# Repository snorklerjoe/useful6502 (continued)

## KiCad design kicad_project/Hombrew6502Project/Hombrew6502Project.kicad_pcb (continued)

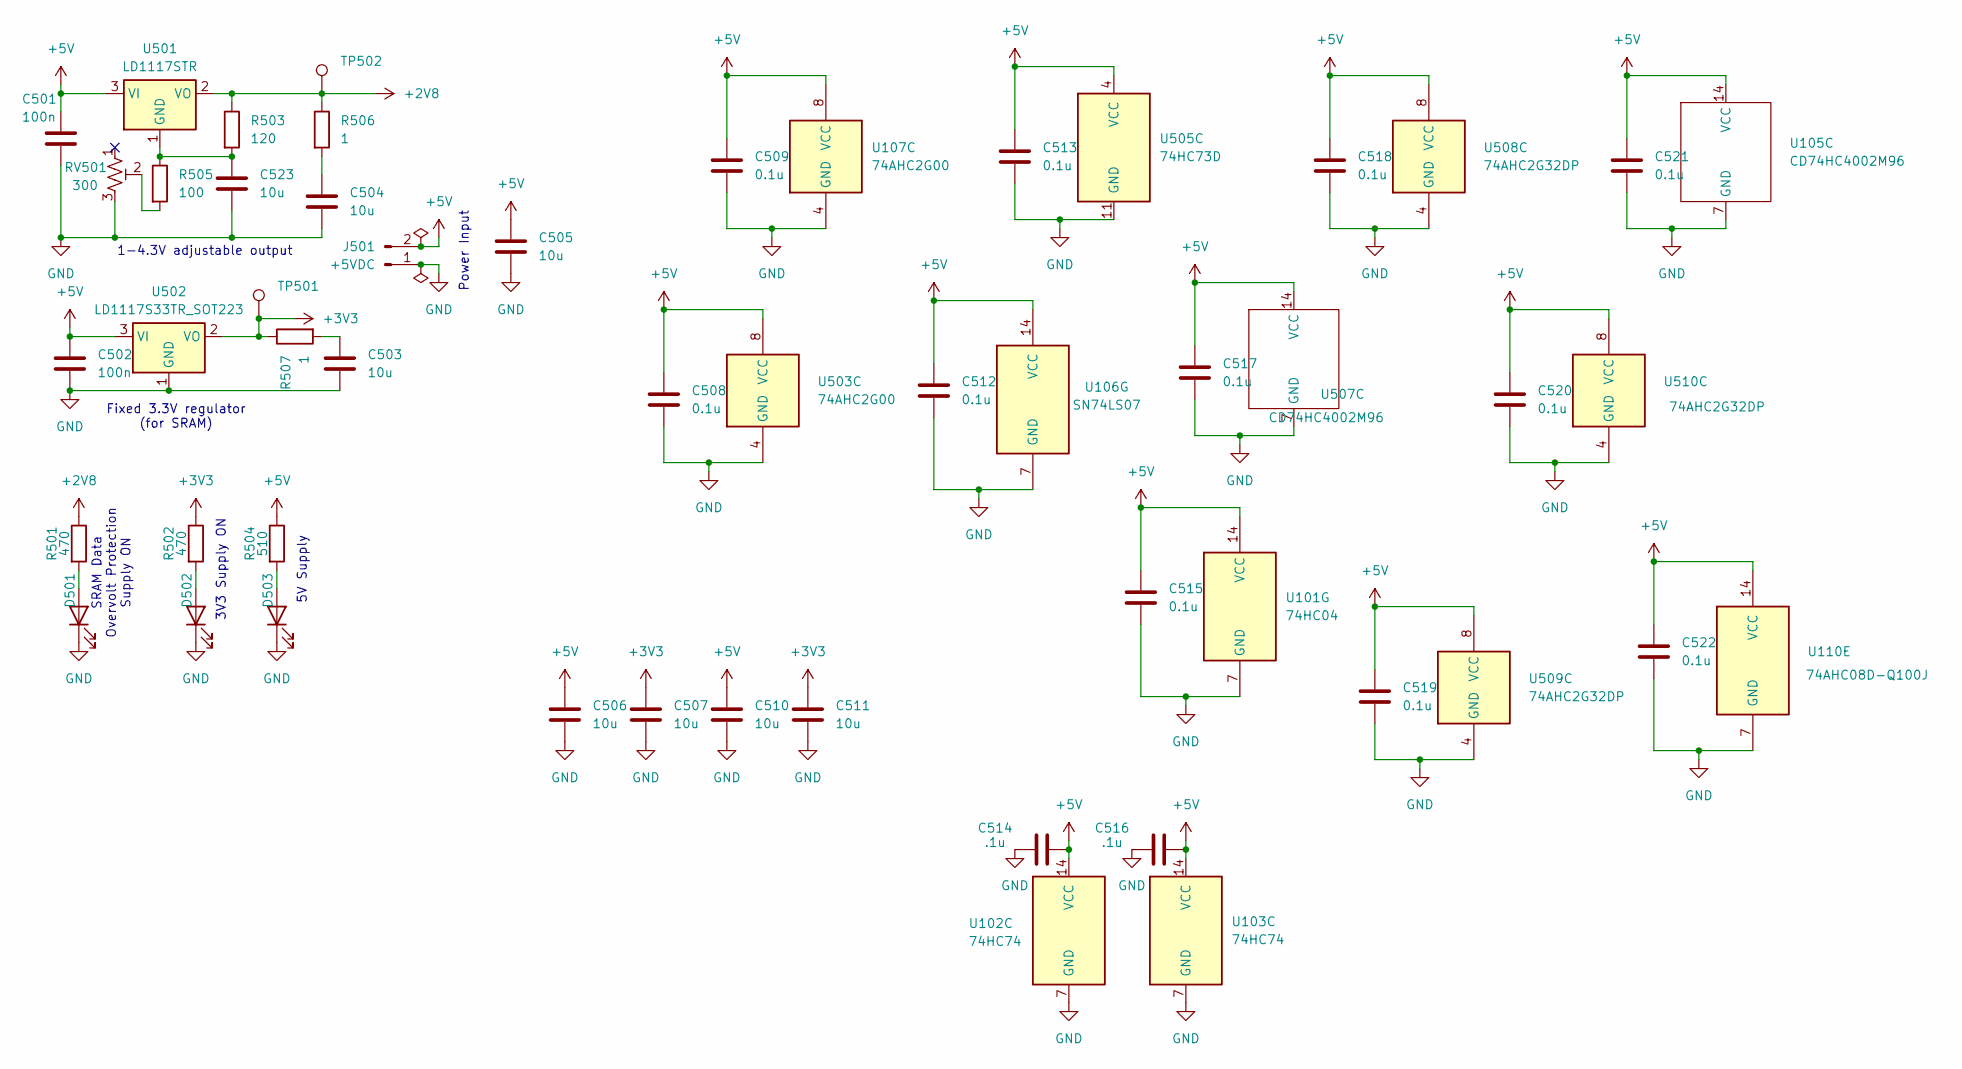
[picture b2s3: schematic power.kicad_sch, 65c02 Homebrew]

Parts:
C501, C502: 100n; C_0402_1005Metric
C503, C504, C505, C506, C507, C510, C511, C523: 10u; C_0402_1005Metric
C508, C509, C512, C513, C515, C517, C518, C519, C520, C521, C522: 0.1u; C_0402_1005Metric
C514, C516: .1u; C_0402_1005Metric
D501, D502, D503: LED; LED_0402_1005Metric
J501: +5VDC; PinHeader_1x02_P2.54mm_Vertical
R501, R502: 470; R_0402_1005Metric
R503: 120; R_0402_1005Metric
R504: 510; R_0402_1005Metric
R505: 100; R_0402_1005Metric
R506, R507: 1; R_0402_1005Metric
RV501: 300; Potentiometer_Bourns_TC33X_Vertical
TP501, TP502: TestPoint; TestPoint_Pad_D2.5mm
U101: 74HC04; SOIC-14_3.9x8.7mm_P1.27mm
U102, U103: 74HC74; SOIC-14_3.9x8.7mm_P1.27mm
U105, U507: CD74HC4002M96; SOIC-14_3.9x8.7mm_P1.27mm
U106: SN74LS07; SOIC-14_3.9x8.7mm_P1.27mm
U107, U503: 74AHC2G00; TSSOP-8_3x3mm_P0.65mm
U110: 74AHC08D-Q100J; SOIC-14_3.9x8.7mm_P1.27mm
U501: LD1117STR; SOT-223-3_TabPin2
U502: LD1117S33TR_SOT223; SOT-223-3_TabPin2
U505: 74HC73D; SOIC-14_3.9x8.7mm_P1.27mm
U508, U509, U510: 74AHC2G32DP; TSSOP-8_3x3mm_P0.65mm

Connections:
+2V8: R501.1, R503.1, R506.1, TP502.1, U501.2 (VO); also elsewhere on the board
+3V3: C507.1, C511.1, R502.1, R507.1, TP501.1, U502.2 (VO); also elsewhere on the board
+5V: C501.1, C502.1, C505.1, C506.1, C508.1, C509.1, C510.1, C512.1, C513.1, C514.1, C515.1, C516.1, C517.1, C518.1, C519.1, C520.1, C521.1, C522.1, J501.2, R504.1, U101.14 (VCC), U102.14 (VCC), U103.14 (VCC), U105.14 (VCC), U106.14 (VCC), U107.8 (VCC), U110.14 (VCC), U501.3 (VI), U502.3 (VI), U503.8 (VCC), U505.4 (VCC), U507.14 (VCC), U508.8 (VCC), U509.8 (VCC), U510.8 (VCC); also elsewhere on the board
GND: C501.2, C502.2, C503.2, C504.2, C505.2, C506.2, C507.2, C508.2, C509.2, C510.2, C511.2, C512.2, C513.2, C514.2, C515.2, C516.2, C517.2, C518.2, C519.2, C520.2, C521.2, C522.2, C523.2, D501.1 (K), D502.1 (K), D503.1 (K), J501.1, RV501.3, U101.7 (GND), U102.7 (GND), U103.7 (GND), U105.7 (GND), U106.7 (GND), U107.4 (GND), U110.7 (GND), U502.1 (GND), U503.4 (GND), U505.11 (GND), U507.7 (GND), U508.4 (GND), U509.4 (GND), U510.4 (GND); also elsewhere on the board
unnamed: C503.1, R507.2
unnamed: C504.1, R506.2
unnamed: D501.2 (A), R501.2
unnamed: D502.2 (A), R502.2
unnamed: D503.2 (A), R504.2
unnamed: R505.2, RV501.2
unnamed: C523.1, R503.2, R505.1, U501.1 (GND)

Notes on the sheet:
Fixed 3.3V regulator (for SRAM)
1-4.3V adjustable output
SRAM Data Overvolt Protection Supply ON
Power Input
5V Supply
3V3 Supply ON

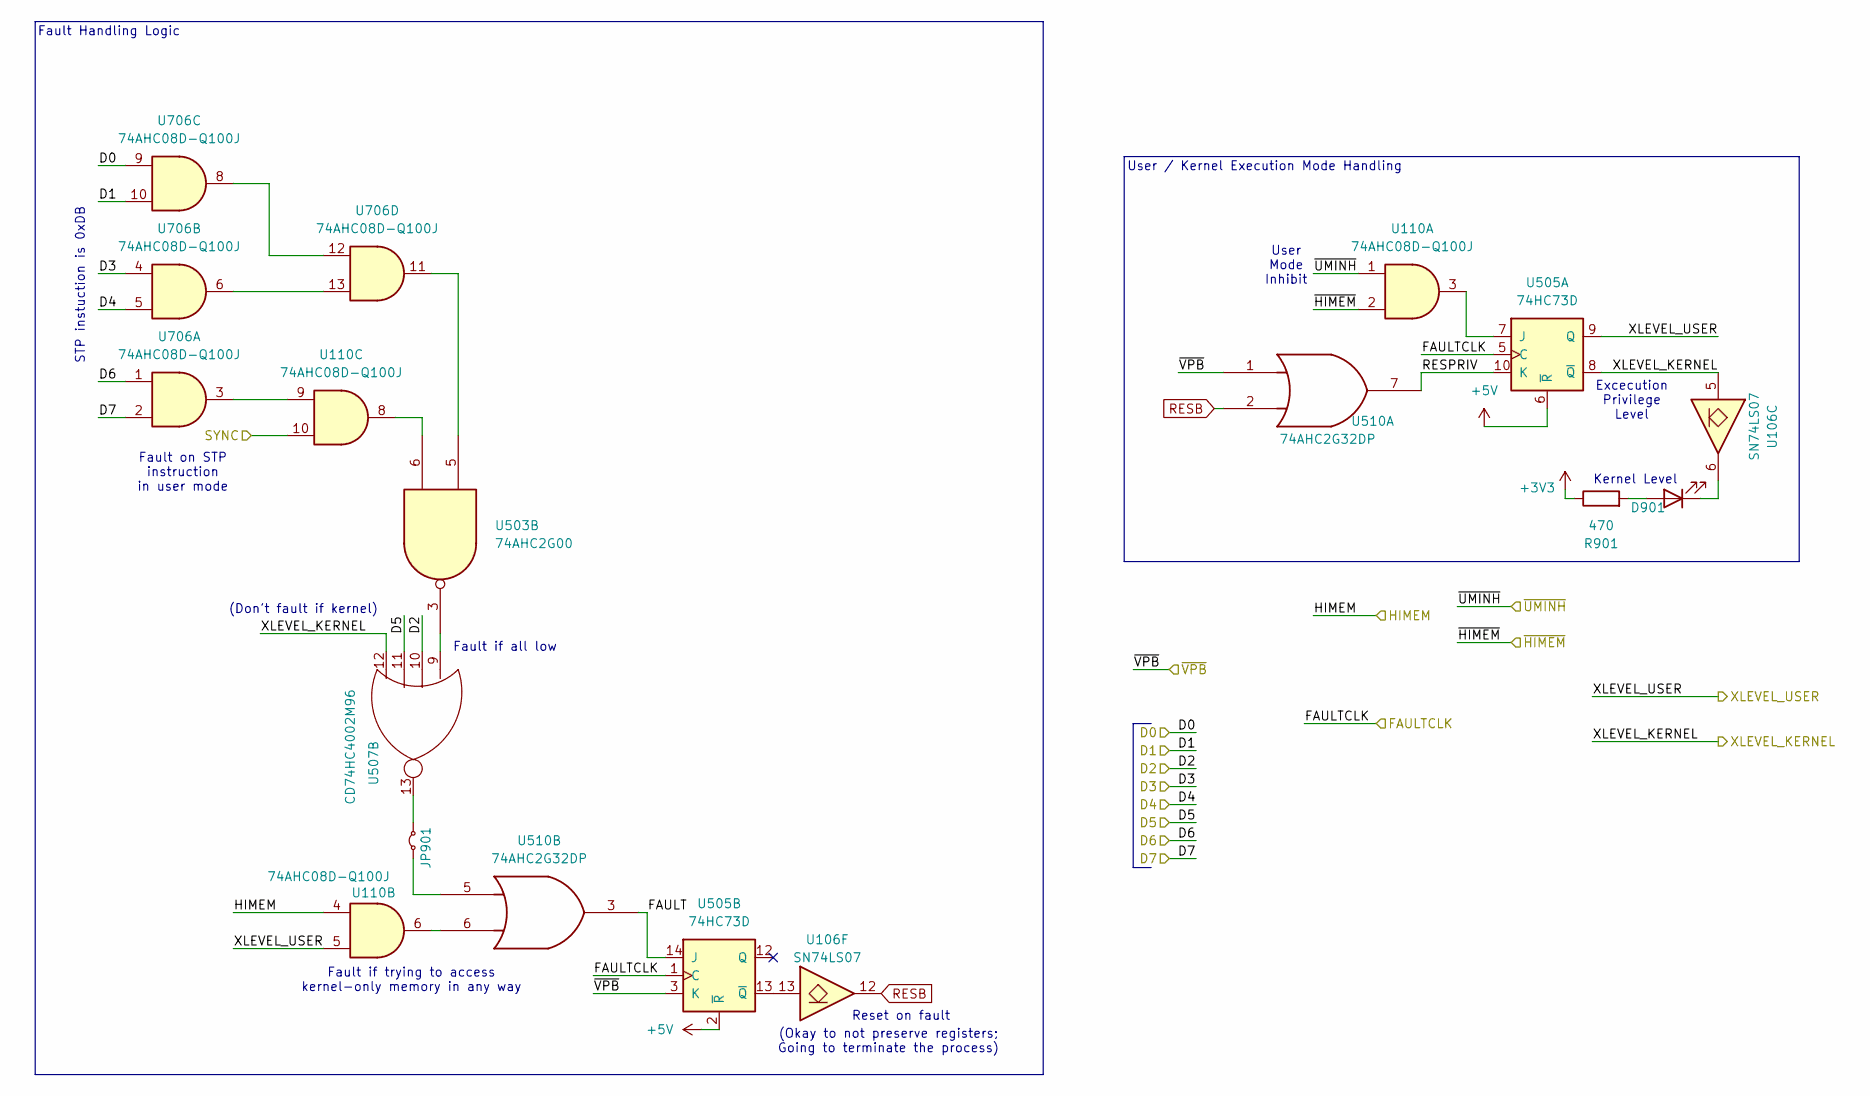
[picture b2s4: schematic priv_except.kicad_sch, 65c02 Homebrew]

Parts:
D901: LED; LED_0402_1005Metric
JP901: Jumper_2_Small_Bridged; SolderJumper-2_P1.3mm_Bridged2Bar_Pad1.0x1.5mm
R901: 470; R_0402_1005Metric
U106: SN74LS07; SOIC-14_3.9x8.7mm_P1.27mm
U110, U706: 74AHC08D-Q100J; SOIC-14_3.9x8.7mm_P1.27mm
U503: 74AHC2G00; TSSOP-8_3x3mm_P0.65mm
U505: 74HC73D; SOIC-14_3.9x8.7mm_P1.27mm
U507: CD74HC4002M96; SOIC-14_3.9x8.7mm_P1.27mm
U510: 74AHC2G32DP; TSSOP-8_3x3mm_P0.65mm

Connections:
+3V3: R901.1; also elsewhere on the board
+5V: U505.2 (~R), U505.6 (~R); also elsewhere on the board
/D0: U706.9; also elsewhere on the board
/D1: U706.10; also elsewhere on the board
/D2: U507.10; also elsewhere on the board
/D3: U706.4; also elsewhere on the board
/D4: U706.5; also elsewhere on the board
/D5: U507.11; also elsewhere on the board
/D6: U706.1; also elsewhere on the board
/D7: U706.2; also elsewhere on the board
/FAULTCLK: U505.1 (C), U505.5 (C); also elsewhere on the board
/HIMEM: U110.4; also elsewhere on the board
/Privileges & Exception Handling/FAULT: U505.14 (J), U510.3
/Privileges & Exception Handling/RESPRIV: U505.10 (K), U510.7
/SYNC: U110.10; also elsewhere on the board
/XLEVEL_KERNEL: U106.5, U505.8 (~Q), U507.12
/XLEVEL_USER: U110.5, U505.9 (Q)
/~HIMEM: U110.2; also elsewhere on the board
/~UMINH: U110.1; also elsewhere on the board
/~VPB: U505.3 (K), U510.1; also elsewhere on the board
unnamed: D901.2 (A), R901.2
unnamed: D901.1 (K), U106.6
unnamed: JP901.1 (A), U510.5
unnamed: JP901.2 (B), U507.13
unnamed: U110.6, U510.6
unnamed: U110.8, U503.6
unnamed: U110.9, U706.3
unnamed: U503.3, U507.9
unnamed: U503.5, U706.11
unnamed: U110.3, U505.7 (J)
unnamed: U106.13, U505.13 (~Q)
unnamed: U706.8, U706.12
unnamed: U706.6, U706.13
RESB: U106.12, U510.2; also elsewhere on the board

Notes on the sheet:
User Mode Inhibit
Kernel Level
Fault if trying to access kernel-only memory in any way
User / Kernel Execution Mode Handling
(Don't fault if kernel)
Fault if all low
Reset on fault
(Okay to not preserve registers; Going to terminate the process)
Fault on STP instruction in user mode
STP instuction is 0xDB
Excecution Privilege Level
Fault Handling Logic

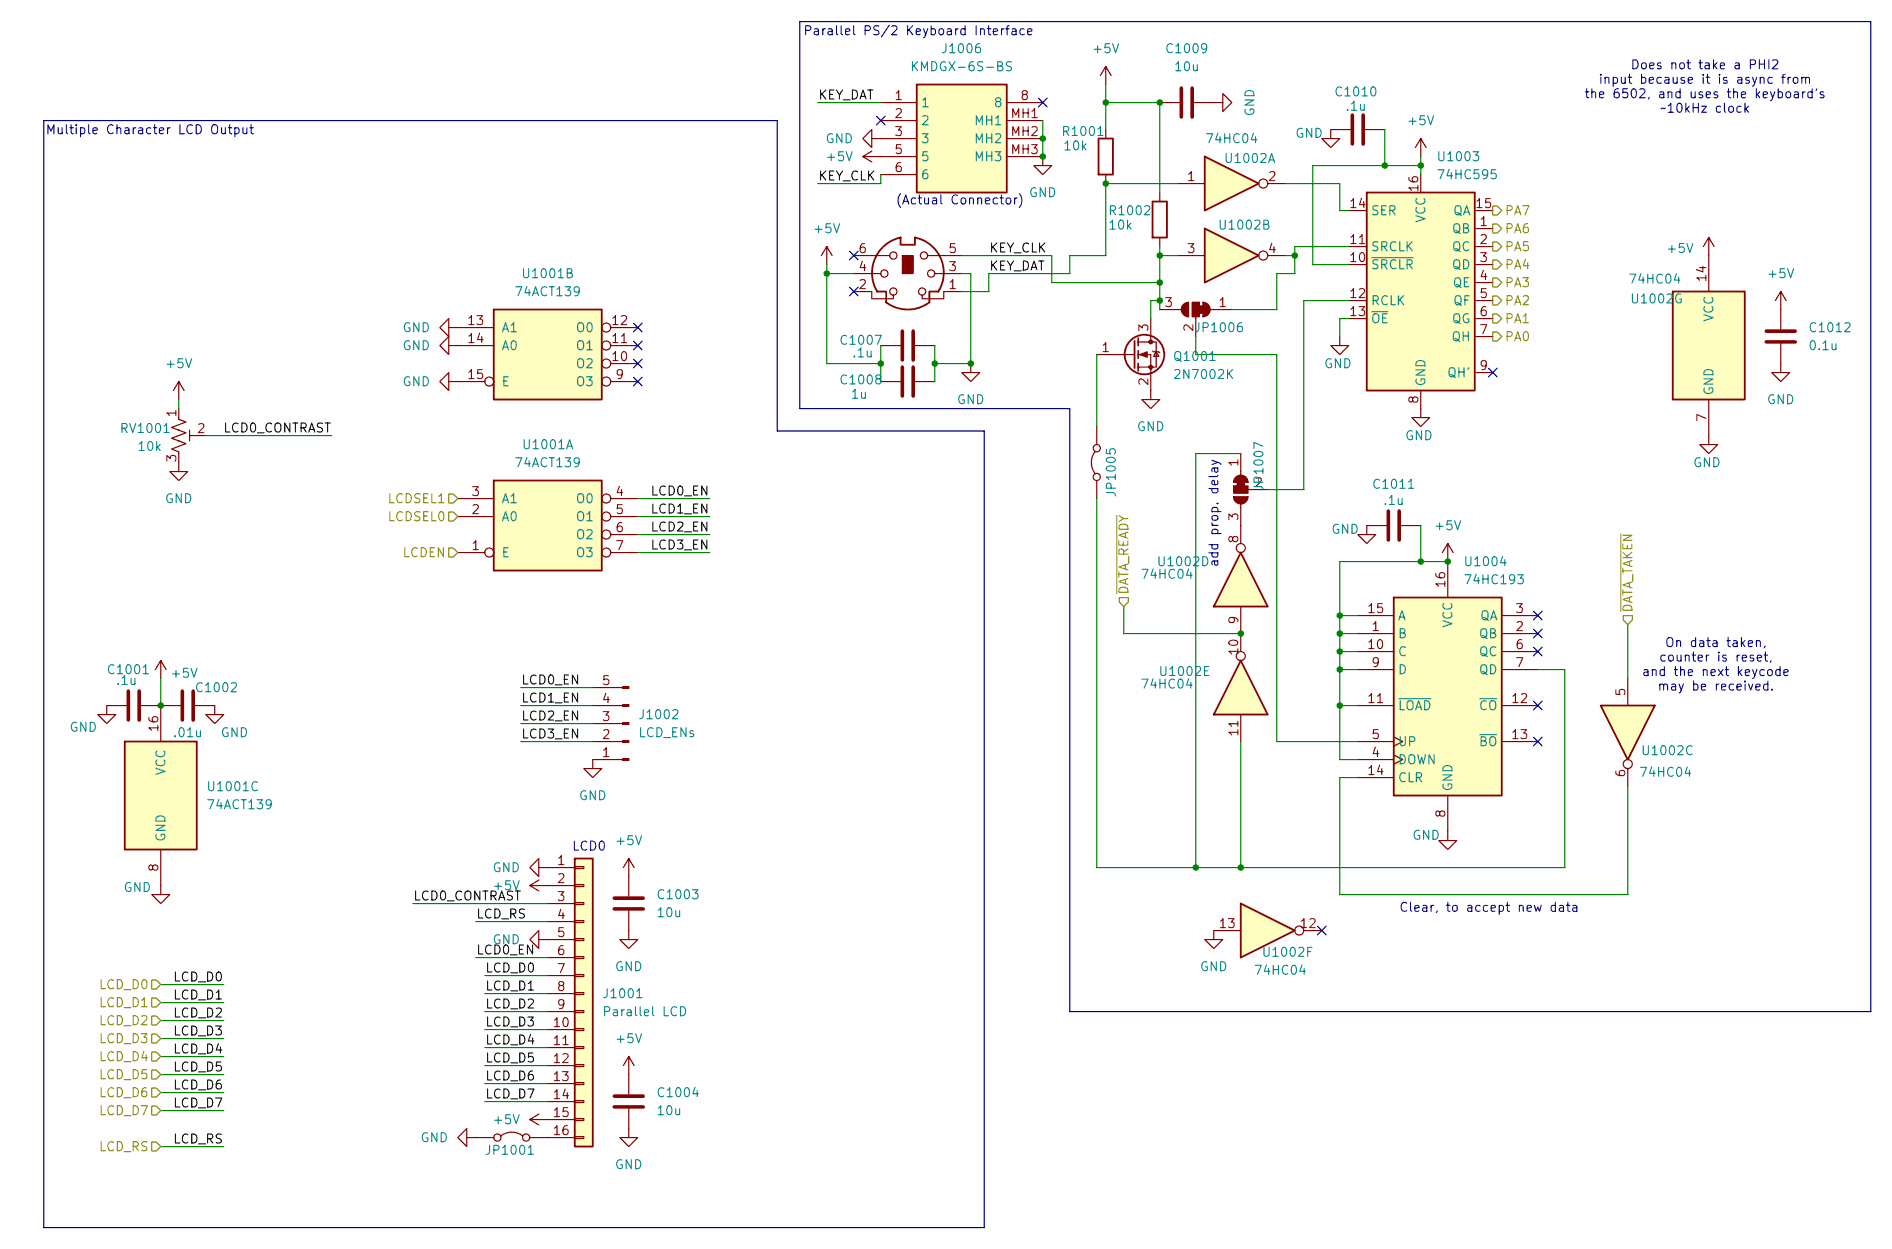
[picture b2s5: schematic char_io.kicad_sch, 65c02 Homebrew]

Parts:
C1001, C1007, C1010, C1011: .1u; C_0402_1005Metric
C1002: .01u; C_0402_1005Metric
C1003, C1004, C1009: 10u; C_0402_1005Metric
C1008: 1u; C_0402_1005Metric
C1012: 0.1u; C_0402_1005Metric
J1001: Parallel LCD; IDC-Header_2x08_P2.54mm_Vertical_SMD
J1002: LCD_ENs; PinHeader_1x05_P2.54mm_Vertical
J1005: KMDGX-6S-BS
J1006: KMDGX-6S-BS; KMDGX6SBS; Mouser Part Number 806-KMDGX-6S-BS
JP1001, JP1005: Jumper_2_Bridged; SolderJumper-2_P1.3mm_Bridged2Bar_Pad1.0x1.5mm
JP1006, JP1007: SolderJumper_3_Bridged12; SolderJumper-3_P1.3mm_Bridged12_Pad1.0x1.5mm
Q1001: 2N7002K; SOT-23
R1001, R1002: 10k; R_0402_1005Metric
RV1001: 10k; Potentiometer_Bourns_TC33X_Vertical
U1001: 74ACT139; TSSOP-16_4.4x5mm_P0.65mm
U1002: 74HC04; SOIC-14_3.9x8.7mm_P1.27mm
U1003: 74HC595; SOIC-16_3.9x9.9mm_P1.27mm
U1004: 74HC193; TSSOP-16_4.4x5mm_P0.65mm

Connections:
+5V: C1001.2, C1002.1, C1003.1, C1004.1, C1007.1, C1008.1, C1009.1, C1010.2, C1011.2, C1012.1, J1001.2, J1001.15, J1005.4, J1006.5, R1001.1, R1002.1, RV1001.1, U1001.16 (VCC), U1002.14 (VCC), U1003.10 (~SRCLR), U1003.16 (VCC), U1004.1 (B), U1004.4 (DOWN), U1004.9 (D), U1004.10 (C), U1004.11 (~LOAD), U1004.15 (A), U1004.16 (VCC); also elsewhere on the board
/Character IO/KEY_CLK: J1005.5, J1006.6, JP1006.3 (B), Q1001.3 (D), R1002.2, U1002.3
/Character IO/KEY_DAT: J1005.1, J1006.1, R1001.2, U1002.1
/Character IO/LCD0_CONTRAST: J1001.3, RV1001.2
/Character IO/LCD0_EN: J1001.6, J1002.5, U1001.4 (O0)
/Character IO/LCD1_EN: J1002.4, U1001.5 (O1)
/Character IO/LCD2_EN: J1002.3, U1001.6 (O2)
/Character IO/LCD3_EN: J1002.2, U1001.7 (O3)
/Character IO/LCDEN: U1001.1 (E); also elsewhere on the board
/Character IO/LCDSEL0: U1001.2 (A0); also elsewhere on the board
/Character IO/LCDSEL1: U1001.3 (A1); also elsewhere on the board
/Character IO/LCD_RS: J1001.4; also elsewhere on the board
/Character IO/PA0: U1003.7 (QH); also elsewhere on the board
/Character IO/PA1: U1003.6 (QG); also elsewhere on the board
/Character IO/PA2: U1003.5 (QF); also elsewhere on the board
/Character IO/PA3: U1003.4 (QE); also elsewhere on the board
/Character IO/PA4: U1003.3 (QD); also elsewhere on the board
/Character IO/PA5: U1003.2 (QC); also elsewhere on the board
/Character IO/PA6: U1003.1 (QB); also elsewhere on the board
/Character IO/PA7: U1003.15 (QA); also elsewhere on the board
/Character IO/~DATA_READY: U1002.9, U1002.10; also elsewhere on the board
/Character IO/~DATA_TAKEN: U1002.5; also elsewhere on the board
/PQ0: J1001.7; also elsewhere on the board
/PQ1: J1001.8; also elsewhere on the board
/PQ2: J1001.9; also elsewhere on the board
/PQ3: J1001.10; also elsewhere on the board
/PQ4: J1001.11; also elsewhere on the board
/PQ5: J1001.12; also elsewhere on the board
/PQ6: J1001.13; also elsewhere on the board
/PQ7: J1001.14; also elsewhere on the board
GND: C1001.1, C1002.2, C1003.2, C1004.2, C1007.2, C1008.2, C1009.2, C1010.1, C1011.1, C1012.2, J1001.1, J1001.5, J1002.1, J1005.3, J1006.3, J1006.MH1, J1006.MH2, J1006.MH3, JP1001.1 (A), Q1001.2 (S), RV1001.3, U1001.8 (GND), U1001.13 (A1), U1001.14 (A0), U1001.15 (E), U1002.7 (GND), U1002.13, U1003.8 (GND), U1003.13 (~OE), U1004.8 (GND); also elsewhere on the board
unnamed: J1001.16, JP1001.2 (B)
unnamed: JP1005.1 (A), JP1007.1 (A), U1002.11, U1004.7 (QD)
unnamed: JP1005.2 (B), Q1001.1 (G)
unnamed: JP1006.1 (A), U1002.4, U1003.11 (SRCLK)
unnamed: JP1006.2 (C), U1004.5 (UP)
unnamed: JP1007.3 (B), U1002.8
unnamed: JP1007.2 (C), U1003.12 (RCLK)
unnamed: U1002.2, U1003.14 (SER)
unnamed: U1002.6, U1004.14 (CLR)

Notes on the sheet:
On data taken, counter is reset, and the next keycode may be received.
(Actual Connector)
Clear, to accept new data
Multiple Character LCD Output
Parallel PS/2 Keyboard Interface
add prop. delay
LCD0
Does not take a PHI2 input because it is async from the 6502, and uses the keyboard's ~10kHz clock

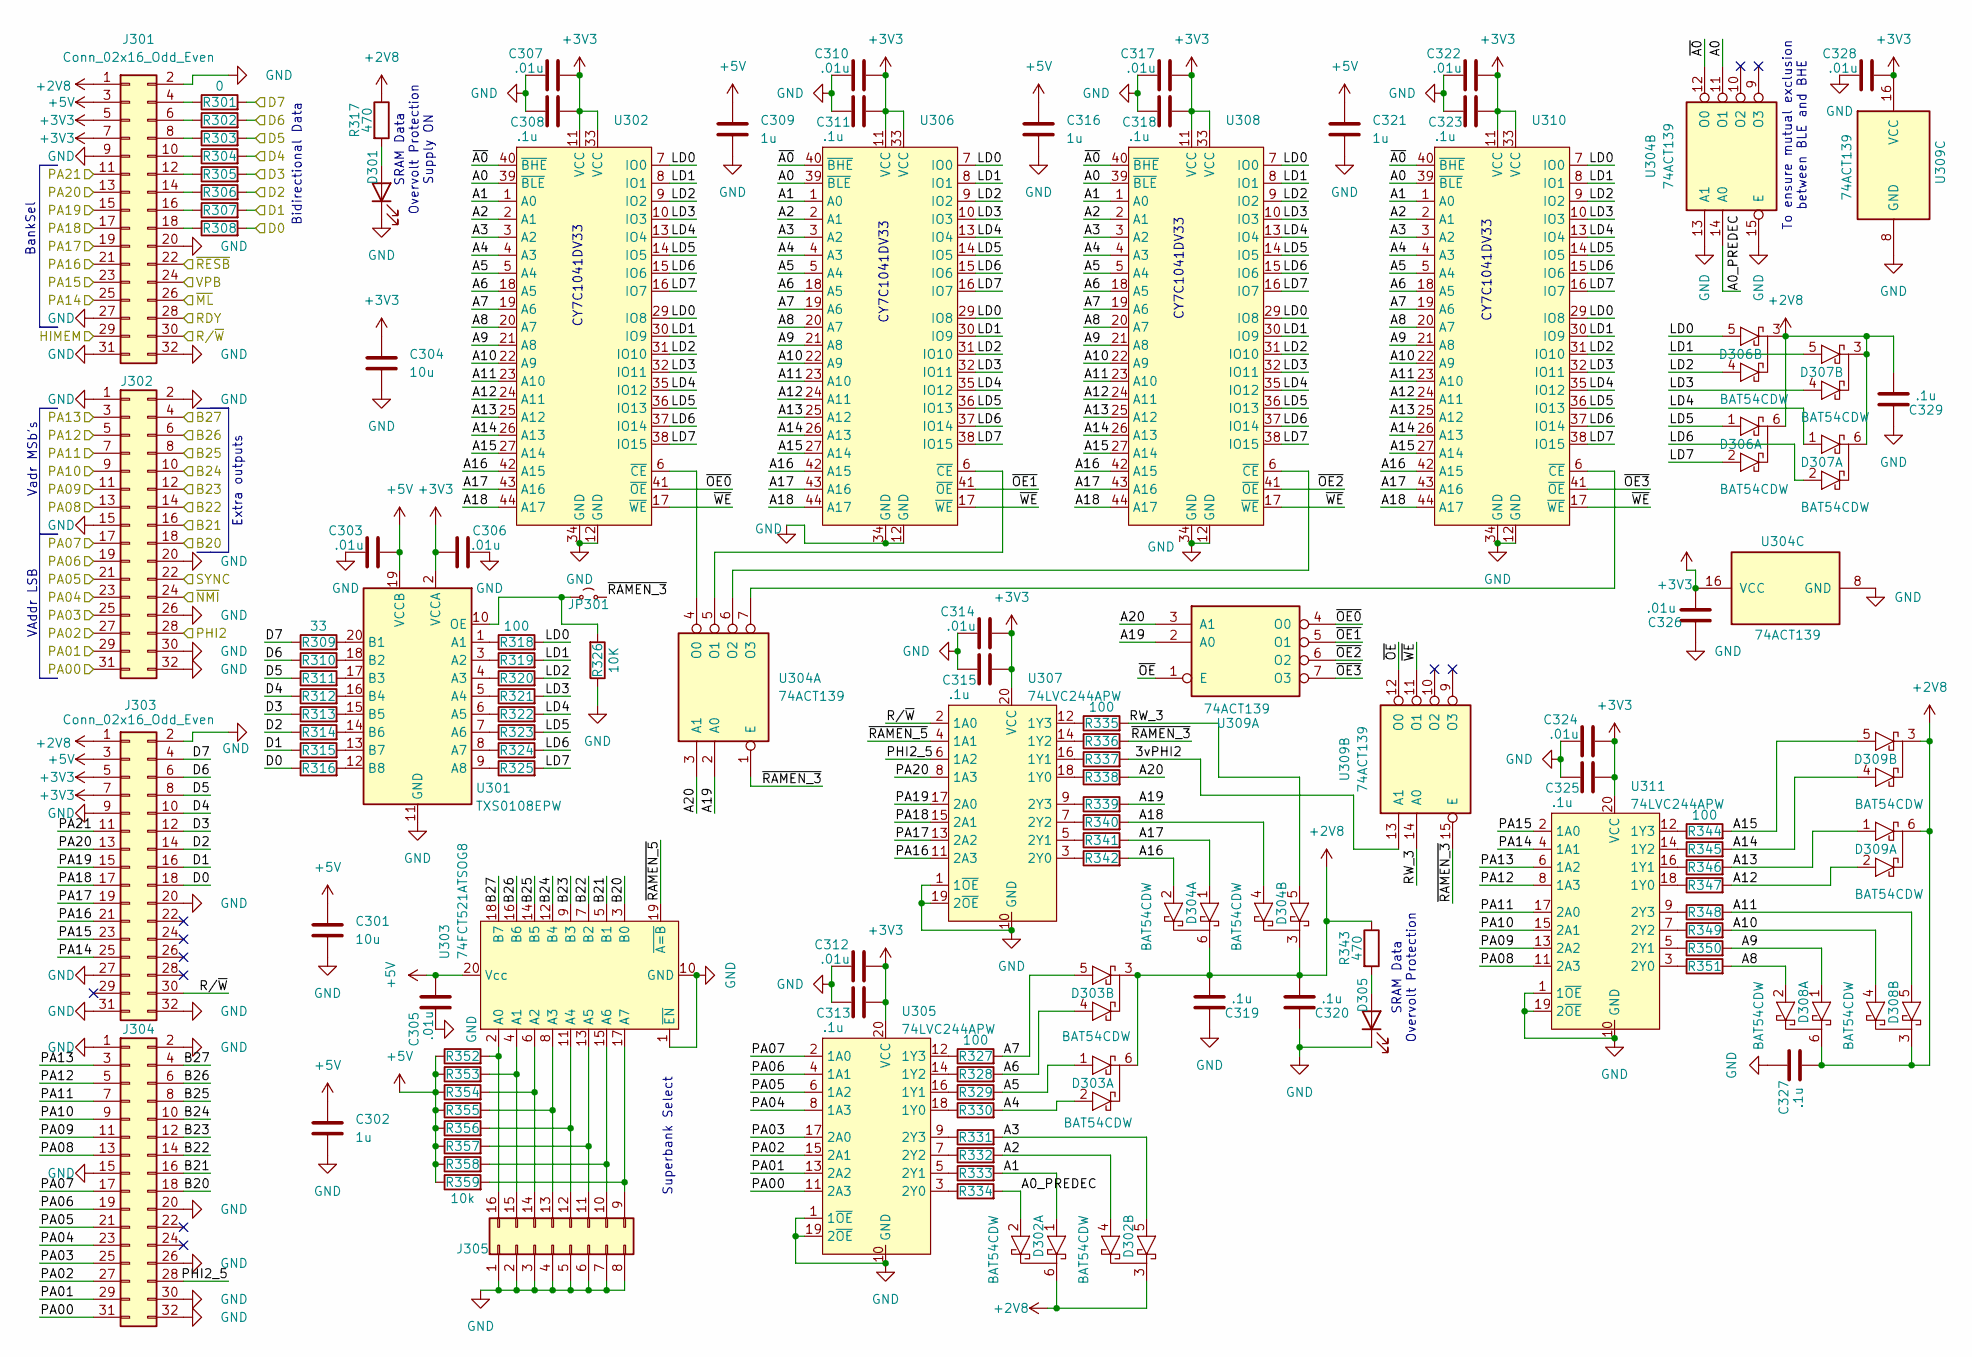
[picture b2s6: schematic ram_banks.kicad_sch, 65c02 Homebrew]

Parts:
C301, C304: 10u; C_0402_1005Metric
C302, C309, C316, C321: 1u; C_0402_1005Metric
C303, C305, C306, C307, C310, C312, C314, C317, C322, C324, C326, C328: .01u; C_0402_1005Metric
C308, C311, C313, C315, C318, C319, C320, C323, C325, C327, C329: .1u; C_0402_1005Metric
D301, D305: LED; LED_0402_1005Metric
D302, D303, D304, D306, D307, D308, D309: BAT54CDW; SOT-363_SC-70-6
J301, J302: Conn_02x16_Odd_Even; PinHeader_2x16_P2.54mm_Vertical
J303, J304: Conn_02x16_Odd_Even; PinHeader_2x16_P2.54mm_Vertical_SMD
J305: Conn_02x08_Counter_Clockwise; PinHeader_2x08_P2.54mm_Vertical_SMD
JP301: Jumper_2_Small_Open; SolderJumper-2_P1.3mm_Open_Pad1.0x1.5mm
R301, R302, R303, R304, R305, R306, R307, R308: 0; R_0402_1005Metric
R309, R310, R311, R312, R313, R314, R315, R316: 33; R_0402_1005Metric
R317, R343: 470; R_0402_1005Metric
R318, R319, R320, R321, R322, R323, R324, R325, R327, R328, R329, R330, R331, R332, R333, R334, R335, R336, R337, R338, R339, R340, R341, R342, R344, R345, R346, R347, R348, R349, R350, R351: 100; R_0402_1005Metric
R326: 10K; R_0402_1005Metric
R352, R353, R354, R355, R356, R357, R358, R359: 10k; R_0402_1005Metric
U301: TXS0108EPW; TSSOP-20_4.4x6.5mm_P0.65mm
U302, U306, U308, U310: TSOP-II-44_10.16x18.41mm_P0.8mm
U303: 74FCT521ATSOG8; SOIC-20W_7.5x12.8mm_P1.27mm
U304, U309: 74ACT139; TSSOP-16_4.4x5mm_P0.65mm
U305, U307, U311: 74LVC244APW; TSSOP-20_4.4x6.5mm_P0.65mm

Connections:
+2V8: C319.1, C320.1, C327.1, C329.1, D302.3 (K2), D302.6 (K2), D303.3 (K2), D303.6 (K2), D304.3 (K2), D304.6 (K2), D306.3 (K2), D306.6 (K2), D307.3 (K2), D307.6 (K2), D308.3 (K2), D308.6 (K2), D309.3 (K2), D309.6 (K2), J301.1, J303.1, R317.1, R343.1; also elsewhere on the board
+3V3: C304.1, C306.1, C307.1, C308.1, C310.1, C311.1, C312.1, C313.1, C314.1, C315.1, C317.1, C318.1, C322.1, C323.1, C324.1, C325.1, C326.1, C328.1, J301.5, J301.7, J303.5, J303.7, U301.2 (VCCA), U302.11 (VCC), U302.33 (VCC), U304.16 (VCC), U305.20 (VCC), U306.11 (VCC), U306.33 (VCC), U307.20 (VCC), U308.11 (VCC), U308.33 (VCC), U309.16 (VCC), U310.11 (VCC), U310.33 (VCC), U311.20 (VCC); also elsewhere on the board
+5V: C301.1, C302.1, C303.1, C305.1, C309.1, C316.1, C321.1, J301.3, J303.3, R352.1, R353.1, R354.1, R355.1, R356.1, R357.1, R358.1, R359.1, U301.19 (VCCB), U303.20 (Vcc); also elsewhere on the board
/A0: J302.31, J304.31, U305.11 (2A3); also elsewhere on the board
/A1: J302.29, J304.29, U305.13 (2A2); also elsewhere on the board
/A2: J302.27, J304.27, U305.15 (2A1); also elsewhere on the board
/A3: J302.25, J304.25, U305.17 (2A0); also elsewhere on the board
/A4: J302.23, J304.23, U305.8 (1A3); also elsewhere on the board
/A5: J302.21, J304.21, U305.6 (1A2); also elsewhere on the board
/A6: J302.19, J304.19, U305.4 (1A1); also elsewhere on the board
/A7: J302.17, J304.17, U305.2 (1A0); also elsewhere on the board
/A8: J302.13, J304.13, U311.11 (2A3); also elsewhere on the board
/A9: J302.11, J304.11, U311.13 (2A2); also elsewhere on the board
/A10: J302.9, J304.9, U311.15 (2A1); also elsewhere on the board
/A11: J302.7, J304.7, U311.17 (2A0); also elsewhere on the board
/A12: J302.5, J304.5, U311.8 (1A3); also elsewhere on the board
/A13: J302.3, J304.3, U311.6 (1A2); also elsewhere on the board
/HIMEM: J301.29; also elsewhere on the board
/RAMCLK: J302.28; also elsewhere on the board
/RDY: J301.28; also elsewhere on the board
/R~W: J301.30, J303.30, U307.2 (1A0); also elsewhere on the board
/SRAM Banks/3vPHI2: R337.2, U309.13 (A1)
/SRAM Banks/A0: U302.39 (~BLE), U304.11 (O1), U306.39 (~BLE), U308.39 (~BLE), U310.39 (~BLE)
/SRAM Banks/A0_PREDEC: D302.2 (A02), R334.2, U304.14 (A0)
/SRAM Banks/A1: D302.1 (A01), R333.2, U302.1 (A0), U306.1 (A0), U308.1 (A0), U310.1 (A0)
/SRAM Banks/A2: D302.4 (A02), R332.2, U302.2 (A1), U306.2 (A1), U308.2 (A1), U310.2 (A1)
/SRAM Banks/A3: D302.5 (A12), R331.2, U302.3 (A2), U306.3 (A2), U308.3 (A2), U310.3 (A2)
/SRAM Banks/A4: D303.2 (A02), R330.2, U302.4 (A3), U306.4 (A3), U308.4 (A3), U310.4 (A3)
/SRAM Banks/A5: D303.1 (A01), R329.2, U302.5 (A4), U306.5 (A4), U308.5 (A4), U310.5 (A4)
/SRAM Banks/A6: D303.4 (A02), R328.2, U302.18 (A5), U306.18 (A5), U308.18 (A5), U310.18 (A5)
/SRAM Banks/A7: D303.5 (A12), R327.2, U302.19 (A6), U306.19 (A6), U308.19 (A6), U310.19 (A6)
/SRAM Banks/A8: D308.2 (A02), R351.2, U302.20 (A7), U306.20 (A7), U308.20 (A7), U310.20 (A7)
/SRAM Banks/A9: D308.1 (A01), R350.2, U302.21 (A8), U306.21 (A8), U308.21 (A8), U310.21 (A8)
/SRAM Banks/A10: D308.4 (A02), R349.2, U302.22 (A9), U306.22 (A9), U308.22 (A9), U310.22 (A9)
/SRAM Banks/A11: D308.5 (A12), R348.2, U302.23 (A10), U306.23 (A10), U308.23 (A10), U310.23 (A10)
/SRAM Banks/A12: D309.2 (A02), R347.2, U302.24 (A11), U306.24 (A11), U308.24 (A11), U310.24 (A11)
/SRAM Banks/A13: D309.1 (A01), R346.2, U302.25 (A12), U306.25 (A12), U308.25 (A12), U310.25 (A12)
/SRAM Banks/A14: D309.4 (A02), R345.2, U302.26 (A13), U306.26 (A13), U308.26 (A13), U310.26 (A13)
/SRAM Banks/A15: D309.5 (A12), R344.2, U302.27 (A14), U306.27 (A14), U308.27 (A14), U310.27 (A14)
/SRAM Banks/A16: D304.2 (A02), R342.2, U302.42 (A15), U306.42 (A15), U308.42 (A15), U310.42 (A15)
/SRAM Banks/A17: D304.1 (A01), R341.2, U302.43 (A16), U306.43 (A16), U308.43 (A16), U310.43 (A16)
/SRAM Banks/A18: D304.4 (A02), R340.2, U302.44 (A17), U306.44 (A17), U308.44 (A17), U310.44 (A17)
/SRAM Banks/A19: R339.2, U304.2 (A0), U309.2 (A0)
/SRAM Banks/A20: R338.2, U304.3 (A1), U309.3 (A1)
/SRAM Banks/B20: J302.18, J304.18, U303.3 (B0); also elsewhere on the board
/SRAM Banks/B21: J302.16, J304.16, U303.5 (B1); also elsewhere on the board
/SRAM Banks/B22: J302.14, J304.14, U303.7 (B2); also elsewhere on the board
/SRAM Banks/B23: J302.12, J304.12, U303.9 (B3); also elsewhere on the board
/SRAM Banks/B24: J302.10, J304.10, U303.12 (B4); also elsewhere on the board
/SRAM Banks/B25: J302.8, J304.8, U303.14 (B5); also elsewhere on the board
/SRAM Banks/B26: J302.6, J304.6, U303.16 (B6); also elsewhere on the board
/SRAM Banks/B27: J302.4, J304.4, U303.18 (B7); also elsewhere on the board
/SRAM Banks/D0: J303.18, R308.2, R316.1; also elsewhere on the board
/SRAM Banks/D1: J303.16, R307.2, R315.1; also elsewhere on the board
/SRAM Banks/D2: J303.14, R306.2, R314.1; also elsewhere on the board
/SRAM Banks/D3: J303.12, R305.2, R313.1; also elsewhere on the board
/SRAM Banks/D4: J303.10, R304.2, R312.1; also elsewhere on the board
/SRAM Banks/D5: J303.8, R303.2, R311.1; also elsewhere on the board
/SRAM Banks/D6: J303.6, R302.2, R310.1; also elsewhere on the board
/SRAM Banks/D7: J303.4, R301.2, R309.1; also elsewhere on the board
/SRAM Banks/LD0: D306.5 (A12), R318.2, U302.7 (IO0), U302.29 (IO8), U306.7 (IO0), U306.29 (IO8), U308.7 (IO0), U308.29 (IO8), U310.7 (IO0), U310.29 (IO8)
/SRAM Banks/LD1: D307.5 (A12), R319.2, U302.8 (IO1), U302.30 (IO9), U306.8 (IO1), U306.30 (IO9), U308.8 (IO1), U308.30 (IO9), U310.8 (IO1), U310.30 (IO9)
/SRAM Banks/LD2: D306.4 (A02), R320.2, U302.9 (IO2), U302.31 (IO10), U306.9 (IO2), U306.31 (IO10), U308.9 (IO2), U308.31 (IO10), U310.9 (IO2), U310.31 (IO10)
/SRAM Banks/LD3: D307.4 (A02), R321.2, U302.10 (IO3), U302.32 (IO11), U306.10 (IO3), U306.32 (IO11), U308.10 (IO3), U308.32 (IO11), U310.10 (IO3), U310.32 (IO11)
/SRAM Banks/LD4: D307.1 (A01), R322.2, U302.13 (IO4), U302.35 (IO12), U306.13 (IO4), U306.35 (IO12), U308.13 (IO4), U308.35 (IO12), U310.13 (IO4), U310.35 (IO12)
/SRAM Banks/LD5: D306.1 (A01), R323.2, U302.14 (IO5), U302.36 (IO13), U306.14 (IO5), U306.36 (IO13), U308.14 (IO5), U308.36 (IO13), U310.14 (IO5), U310.36 (IO13)
/SRAM Banks/LD6: D307.2 (A02), R324.2, U302.15 (IO6), U302.37 (IO14), U306.15 (IO6), U306.37 (IO14), U308.15 (IO6), U308.37 (IO14), U310.15 (IO6), U310.37 (IO14)
/SRAM Banks/LD7: D306.2 (A02), R325.2, U302.16 (IO7), U302.38 (IO15), U306.16 (IO7), U306.38 (IO15), U308.16 (IO7), U308.38 (IO15), U310.16 (IO7), U310.38 (IO15)
/SRAM Banks/PA14: J301.25, J303.25, U311.4 (1A1); also elsewhere on the board
/SRAM Banks/PA15: J301.23, J303.23, U311.2 (1A0); also elsewhere on the board
/SRAM Banks/PA16: J301.21, J303.21, U307.11 (2A3); also elsewhere on the board
/SRAM Banks/PA17: J301.19, J303.19, U307.13 (2A2); also elsewhere on the board
/SRAM Banks/PA18: J301.17, J303.17, U307.15 (2A1); also elsewhere on the board
/SRAM Banks/PA19: J301.15, J303.15, U307.17 (2A0); also elsewhere on the board
/SRAM Banks/PA20: J301.13, J303.13, U307.8 (1A3); also elsewhere on the board
/SRAM Banks/PA21: J301.11, J303.11; also elsewhere on the board
/SRAM Banks/PHI2_5: J304.28, U307.6 (1A2)
/SRAM Banks/RW_3: D304.5 (A12), R335.2, U309.14 (A0)
/SRAM Banks/~A0: U302.40 (~BHE), U304.12 (O0), U306.40 (~BHE), U308.40 (~BHE), U310.40 (~BHE)
/SRAM Banks/~OE0: U302.41 (~OE), U309.4 (O0)
/SRAM Banks/~OE1: U306.41 (~OE), U309.5 (O1)
/SRAM Banks/~OE2: U308.41 (~OE), U309.6 (O2)
/SRAM Banks/~OE3: U309.7 (O3), U310.41 (~OE)
/SRAM Banks/~OE: U309.1 (E), U309.12 (O0)
/SRAM Banks/~RAMEN_3: JP301.2 (B), R336.2, U304.1 (E), U309.15 (E)
/SRAM Banks/~RAMEN_5: U303.19 (~A=B), U307.4 (1A1)
/SRAM Banks/~WE: U302.17 (~WE), U306.17 (~WE), U308.17 (~WE), U309.11 (O1), U310.17 (~WE)
/SYNC: J302.22; also elsewhere on the board
/~ML: J301.26; also elsewhere on the board
/~NMI: J302.24; also elsewhere on the board
/~VPB: J301.24; also elsewhere on the board
GND: C301.2, C302.2, C303.2, C304.2, C305.2, C306.2, C307.2, C308.2, C309.2, C310.2, C311.2, C312.2, C313.2, C314.2, C315.2, C316.2, C317.2, C318.2, C319.2, C320.2, C321.2, C322.2, C323.2, C324.2, C325.2, C326.2, C327.2, C328.2, C329.2, D301.1 (K), D305.1 (K), J301.2, J301.9, J301.20, J301.27, J301.31, J301.32, J302.1, J302.2, J302.15, J302.20, J302.26, J302.30, J302.32, J303.2, J303.9, J303.20, J303.27, J303.31, J303.32, J304.1, J304.2, J304.15, J304.20, J304.26, J304.30, J304.32, J305.1, J305.2, J305.3, J305.4, J305.5, J305.6, J305.7, J305.8, R326.1, U301.11 (GND), U302.12 (GND), U302.34 (GND), U303.1 (~EN), U303.10 (GND), U304.8 (GND), U304.13 (A1), U304.15 (E), U305.1 (1~OE), U305.10 (GND), U305.19 (2~OE), U306.12 (GND), U306.34 (GND), U307.1 (1~OE), U307.10 (GND), U307.19 (2~OE), U308.12 (GND), U308.34 (GND), U309.8 (GND), U310.12 (GND), U310.34 (GND), U311.1 (1~OE), U311.10 (GND), U311.19 (2~OE); also elsewhere on the board
unnamed: D301.2 (A), R317.2
unnamed: D305.2 (A), R343.2
unnamed: J301.4, R301.1
unnamed: J301.6, R302.1
unnamed: J301.8, R303.1
unnamed: J301.10, R304.1
unnamed: J301.12, R305.1
unnamed: J301.14, R306.1
unnamed: J301.16, R307.1
unnamed: J301.18, R308.1
unnamed: J305.9, R359.2, U303.17 (A7)
unnamed: J305.10, R358.2, U303.15 (A6)
unnamed: J305.11, R357.2, U303.13 (A5)
unnamed: J305.12, R356.2, U303.11 (A4)
unnamed: J305.13, R355.2, U303.8 (A3)
unnamed: J305.14, R354.2, U303.6 (A2)
unnamed: J305.15, R353.2, U303.4 (A1)
unnamed: J305.16, R352.2, U303.2 (A0)
unnamed: JP301.1 (A), R326.2, U301.10 (OE)
unnamed: R318.1, U301.1 (A1)
unnamed: R319.1, U301.3 (A2)
unnamed: R320.1, U301.4 (A3)
unnamed: R321.1, U301.5 (A4)
unnamed: R322.1, U301.6 (A5)
unnamed: R323.1, U301.7 (A6)
unnamed: R324.1, U301.8 (A7)
unnamed: R325.1, U301.9 (A8)
unnamed: R309.2, U301.20 (B1)
unnamed: R310.2, U301.18 (B2)
unnamed: R311.2, U301.17 (B3)
unnamed: R312.2, U301.16 (B4)
unnamed: R313.2, U301.15 (B5)
unnamed: R314.2, U301.14 (B6)
unnamed: R315.2, U301.13 (B7)
unnamed: R316.2, U301.12 (B8)
unnamed: U302.6 (~CE), U304.4 (O0)
unnamed: U304.5 (O1), U306.6 (~CE)
unnamed: U304.6 (O2), U308.6 (~CE)
unnamed: U304.7 (O3), U310.6 (~CE)
unnamed: R330.1, U305.18 (1Y0)
unnamed: R329.1, U305.16 (1Y1)
unnamed: R328.1, U305.14 (1Y2)
unnamed: R327.1, U305.12 (1Y3)
unnamed: R334.1, U305.3 (2Y0)
unnamed: R333.1, U305.5 (2Y1)
unnamed: R332.1, U305.7 (2Y2)
unnamed: R331.1, U305.9 (2Y3)
unnamed: R338.1, U307.18 (1Y0)
unnamed: R337.1, U307.16 (1Y1)
unnamed: R336.1, U307.14 (1Y2)
unnamed: R335.1, U307.12 (1Y3)
unnamed: R342.1, U307.3 (2Y0)
unnamed: R341.1, U307.5 (2Y1)
unnamed: R340.1, U307.7 (2Y2)
unnamed: R339.1, U307.9 (2Y3)
unnamed: R347.1, U311.18 (1Y0)
unnamed: R346.1, U311.16 (1Y1)
unnamed: R345.1, U311.14 (1Y2)
unnamed: R344.1, U311.12 (1Y3)
unnamed: R351.1, U311.3 (2Y0)
unnamed: R350.1, U311.5 (2Y1)
unnamed: R349.1, U311.7 (2Y2)
unnamed: R348.1, U311.9 (2Y3)
RESB: J301.22; also elsewhere on the board

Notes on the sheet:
VAddr LSB
CY7C1041DV33
Bidirectional Data
Vadr MSb's
SRAM Data Overvolt Protection
Superbank Select
Extra outputs
To ensure mutual exclusion between BLE and BHE
SRAM Data Overvolt Protection Supply ON
BankSel
